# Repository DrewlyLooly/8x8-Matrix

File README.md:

# Adafruit-NeoPixel-8x8-Matrix 

__Format is KiCAD schematic and board layout__

Based directly on the Adafuit NeoPixel 8x8 Matrix, this design converts to KiCAD and facilitates direct use with the HAZE flagger kit

## License

Adafruit invests time and resources providing this open source design, 
please support Adafruit and open-source hardware by purchasing 
products from Adafruit!

Designed by Adafruit Industries, modified by Haze Engineering, LLC.  
Creative Commons Attribution, Share-Alike license, check license.txt for more information
All text above must be included in any redistribution

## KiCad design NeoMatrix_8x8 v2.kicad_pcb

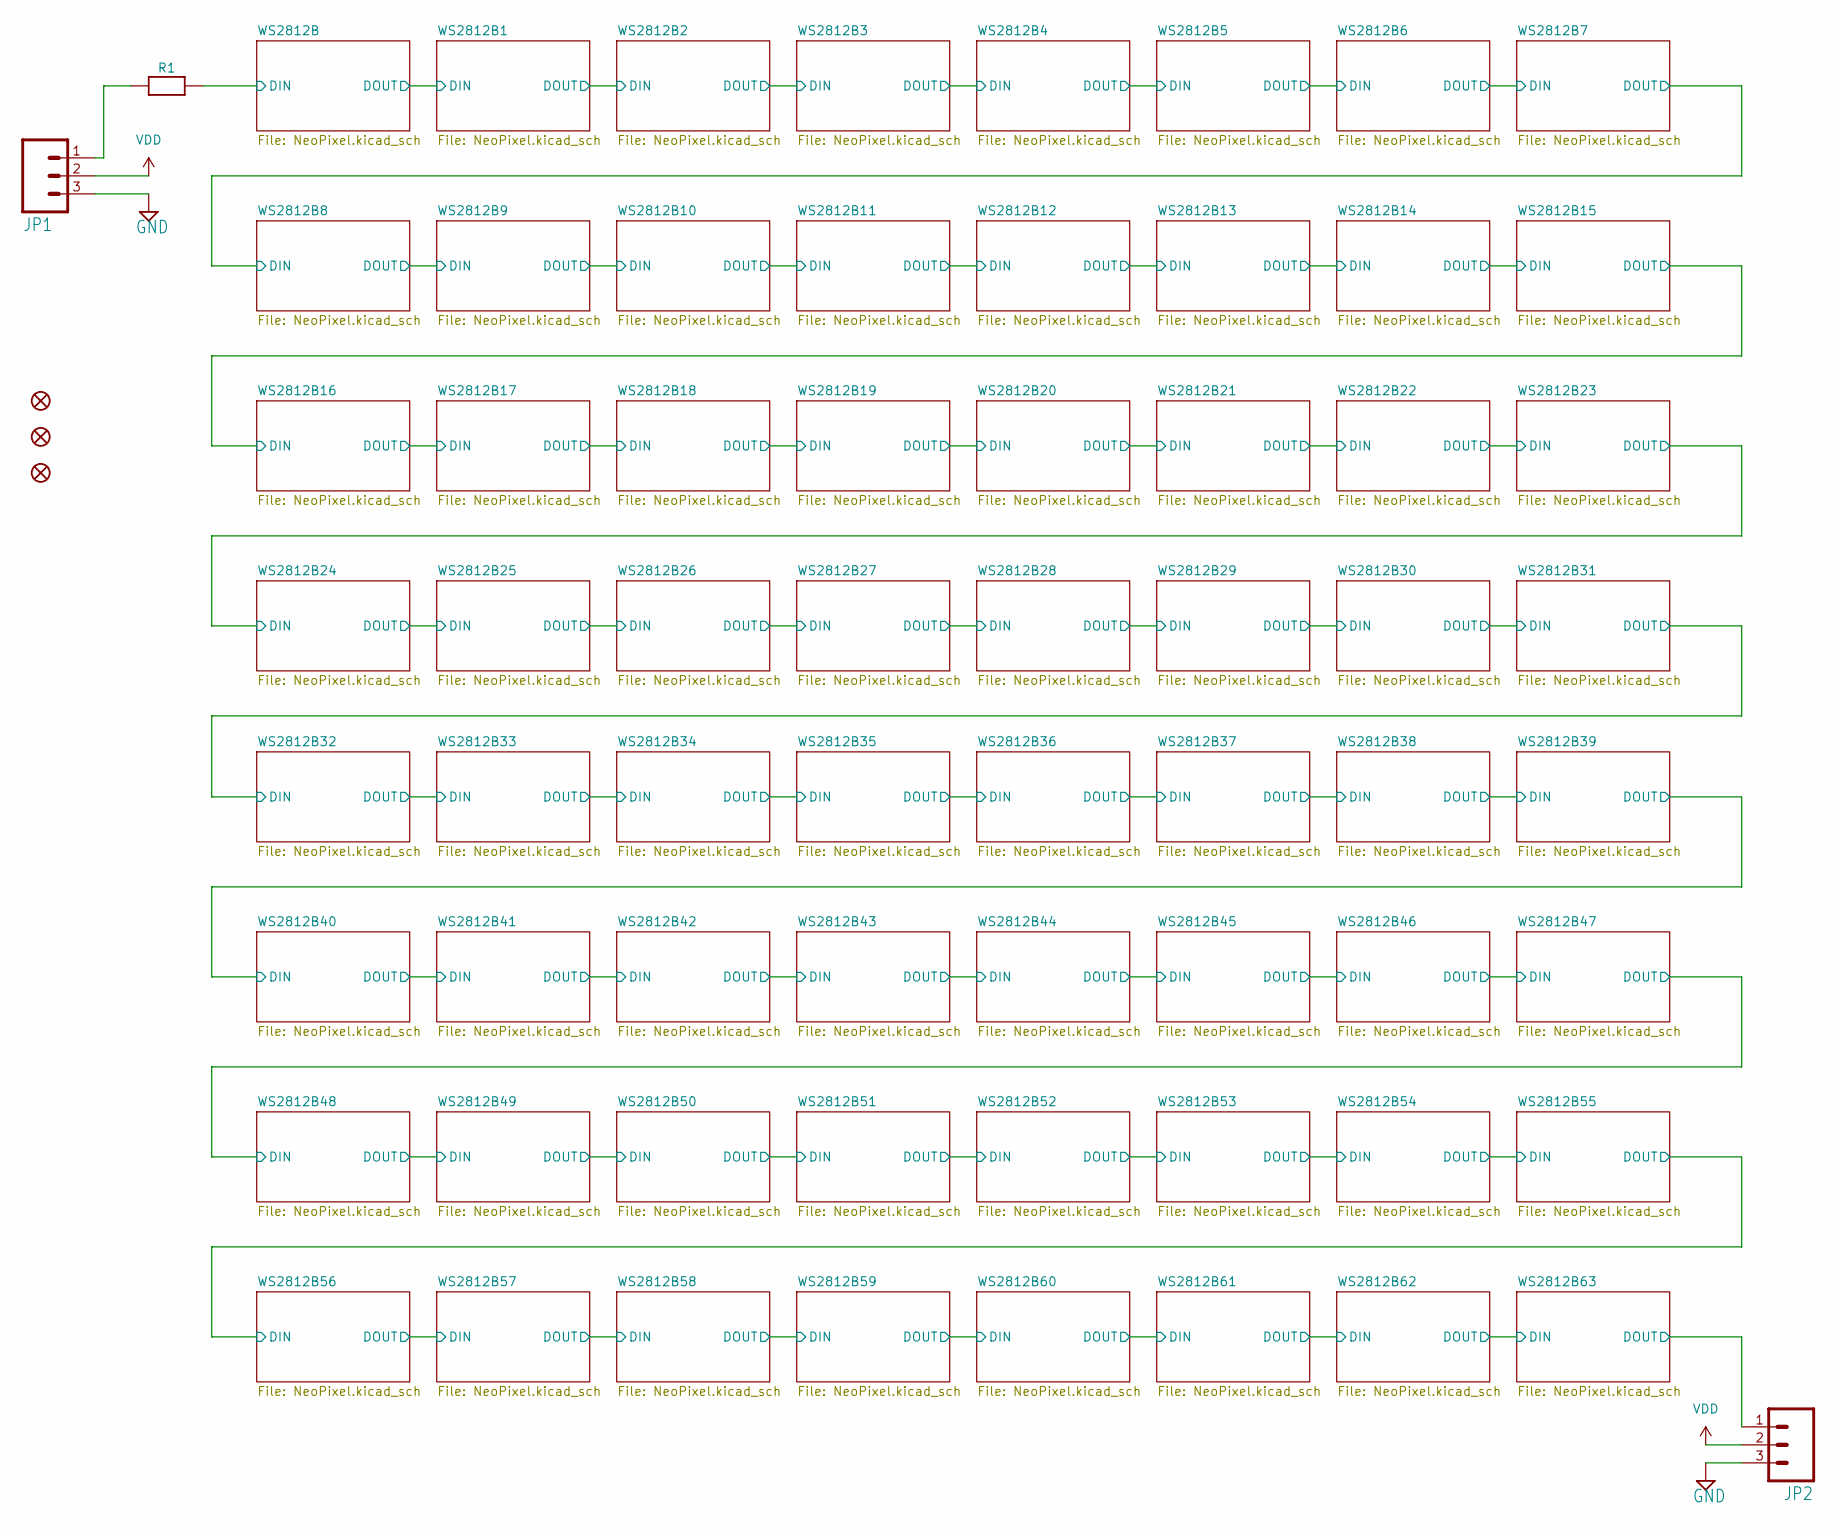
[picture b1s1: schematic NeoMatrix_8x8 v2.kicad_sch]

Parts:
FID1, FID2, FID3: FIDUCIAL""; FIDUCIAL_1MM
JP1, JP2: M03PTH; 1X03
R1: 470R; 0805-NO

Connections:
/WS2812B63/DOUT: JP2.1; also elsewhere on the board
/WS2812B/DIN: R1.2; also elsewhere on the board
GND: JP1.3, JP2.3; also elsewhere on the board
unnamed: JP1.1, R1.1
VDD: JP1.2, JP2.2; also elsewhere on the board

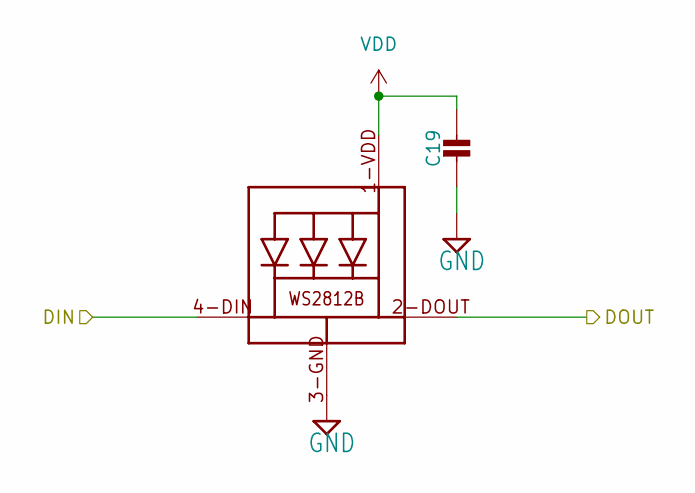
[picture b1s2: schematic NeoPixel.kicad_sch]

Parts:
C19: CAP_CERAMIC0805-NOOUTLINE; 0805-NO
LED19: WS2812B5050; WS2812B

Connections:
/WS2812B17/DOUT: LED19.4-DIN (DI); also elsewhere on the board
/WS2812B18/DOUT: LED19.2-DOUT (DO); also elsewhere on the board
GND: C19.2, LED19.3-GND (GND); also elsewhere on the board
VDD: C19.1, LED19.1-VDD (VDD); also elsewhere on the board

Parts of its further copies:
C1, C2, C3, C4, C5, C6, C7, C9, C10, C11, C12, C13, C14, C15, C17, C18, C20, C21, C22, C23, C25, C26, C27, C28, C29, C30, C31, C33, C34, C35, C36, C37, C38, C39, C41, C42, C43, C44, C45, C46, C47, C49, C50, C51, C52, C53, C54, C55, C57, C58, C59, C60, C61, C62, C63: CAP_CERAMIC0805-NOOUTLINE; 0805-NO
LED1, LED2, LED3, LED4, LED5, LED6, LED7, LED8, LED9, LED10, LED11, LED12, LED13, LED14, LED15, LED16, LED17, LED18, LED20, LED21, LED22, LED23, LED24, LED25, LED26, LED27, LED28, LED29, LED30, LED31, LED32, LED33, LED34, LED35, LED36, LED37, LED38, LED39, LED40, LED41, LED42, LED43, LED44, LED45, LED46, LED47, LED48, LED49, LED50, LED51, LED52, LED53, LED54, LED55, LED56, LED57, LED58, LED59, LED60, LED61, LED62, LED63, LED64: WS2812B5050; WS2812B

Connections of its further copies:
/WS2812B1/DOUT: LED2.2-DOUT (DO), LED3.4-DIN (DI)
/WS2812B2/DOUT: LED3.2-DOUT (DO), LED4.4-DIN (DI)
/WS2812B3/DOUT: LED4.2-DOUT (DO), LED5.4-DIN (DI)
/WS2812B4/DOUT: LED5.2-DOUT (DO), LED6.4-DIN (DI)
/WS2812B5/DOUT: LED6.2-DOUT (DO), LED7.4-DIN (DI)
/WS2812B6/DOUT: LED7.2-DOUT (DO), LED8.4-DIN (DI)
/WS2812B7/DOUT: LED8.2-DOUT (DO), LED9.4-DIN (DI)
/WS2812B8/DOUT: LED9.2-DOUT (DO), LED10.4-DIN (DI)
/WS2812B10/DIN: LED10.2-DOUT (DO), LED11.4-DIN (DI)
/WS2812B10/DOUT: LED11.2-DOUT (DO), LED12.4-DIN (DI)
/WS2812B11/DOUT: LED12.2-DOUT (DO), LED13.4-DIN (DI)
/WS2812B12/DOUT: LED13.2-DOUT (DO), LED14.4-DIN (DI)
/WS2812B13/DOUT: LED14.2-DOUT (DO), LED15.4-DIN (DI)
/WS2812B14/DOUT: LED15.2-DOUT (DO), LED16.4-DIN (DI)
/WS2812B15/DOUT: LED16.2-DOUT (DO), LED17.4-DIN (DI)
/WS2812B16/DOUT: LED17.2-DOUT (DO), LED18.4-DIN (DI)
/WS2812B17/DOUT: LED18.2-DOUT (DO); also elsewhere on the board
/WS2812B18/DOUT: LED20.4-DIN (DI); also elsewhere on the board
/WS2812B19/DOUT: LED20.2-DOUT (DO), LED21.4-DIN (DI)
/WS2812B20/DOUT: LED21.2-DOUT (DO), LED22.4-DIN (DI)
/WS2812B21/DOUT: LED22.2-DOUT (DO), LED23.4-DIN (DI)
/WS2812B22/DOUT: LED23.2-DOUT (DO), LED24.4-DIN (DI)
/WS2812B23/DOUT: LED24.2-DOUT (DO), LED25.4-DIN (DI)
/WS2812B24/DOUT: LED25.2-DOUT (DO), LED26.4-DIN (DI)
/WS2812B25/DOUT: LED26.2-DOUT (DO), LED27.4-DIN (DI)
/WS2812B26/DOUT: LED27.2-DOUT (DO), LED28.4-DIN (DI)
/WS2812B27/DOUT: LED28.2-DOUT (DO), LED29.4-DIN (DI)
/WS2812B28/DOUT: LED29.2-DOUT (DO), LED30.4-DIN (DI)
/WS2812B29/DOUT: LED30.2-DOUT (DO), LED31.4-DIN (DI)
/WS2812B30/DOUT: LED31.2-DOUT (DO), LED32.4-DIN (DI)
/WS2812B31/DOUT: LED32.2-DOUT (DO), LED33.4-DIN (DI)
/WS2812B32/DOUT: LED33.2-DOUT (DO), LED34.4-DIN (DI)
/WS2812B33/DOUT: LED34.2-DOUT (DO), LED35.4-DIN (DI)
/WS2812B34/DOUT: LED35.2-DOUT (DO), LED36.4-DIN (DI)
/WS2812B35/DOUT: LED36.2-DOUT (DO), LED37.4-DIN (DI)
/WS2812B36/DOUT: LED37.2-DOUT (DO), LED38.4-DIN (DI)
/WS2812B37/DOUT: LED38.2-DOUT (DO), LED39.4-DIN (DI)
/WS2812B38/DOUT: LED39.2-DOUT (DO), LED40.4-DIN (DI)
/WS2812B39/DOUT: LED40.2-DOUT (DO), LED41.4-DIN (DI)
/WS2812B40/DOUT: LED41.2-DOUT (DO), LED42.4-DIN (DI)
/WS2812B41/DOUT: LED42.2-DOUT (DO), LED43.4-DIN (DI)
/WS2812B42/DOUT: LED43.2-DOUT (DO), LED44.4-DIN (DI)
/WS2812B43/DOUT: LED44.2-DOUT (DO), LED45.4-DIN (DI)
/WS2812B44/DOUT: LED45.2-DOUT (DO), LED46.4-DIN (DI)
/WS2812B45/DOUT: LED46.2-DOUT (DO), LED47.4-DIN (DI)
/WS2812B46/DOUT: LED47.2-DOUT (DO), LED48.4-DIN (DI)
/WS2812B47/DOUT: LED48.2-DOUT (DO), LED49.4-DIN (DI)
/WS2812B48/DOUT: LED49.2-DOUT (DO), LED50.4-DIN (DI)
/WS2812B49/DOUT: LED50.2-DOUT (DO), LED51.4-DIN (DI)
/WS2812B50/DOUT: LED51.2-DOUT (DO), LED52.4-DIN (DI)
/WS2812B51/DOUT: LED52.2-DOUT (DO), LED53.4-DIN (DI)
/WS2812B52/DOUT: LED53.2-DOUT (DO), LED54.4-DIN (DI)
/WS2812B53/DOUT: LED54.2-DOUT (DO), LED55.4-DIN (DI)
/WS2812B54/DOUT: LED55.2-DOUT (DO), LED56.4-DIN (DI)
/WS2812B55/DOUT: LED56.2-DOUT (DO), LED57.4-DIN (DI)
/WS2812B56/DOUT: LED57.2-DOUT (DO), LED58.4-DIN (DI)
/WS2812B57/DOUT: LED58.2-DOUT (DO), LED59.4-DIN (DI)
/WS2812B58/DOUT: LED59.2-DOUT (DO), LED60.4-DIN (DI)
/WS2812B59/DOUT: LED60.2-DOUT (DO), LED61.4-DIN (DI)
/WS2812B60/DOUT: LED61.2-DOUT (DO), LED62.4-DIN (DI)
/WS2812B61/DOUT: LED62.2-DOUT (DO), LED63.4-DIN (DI)
/WS2812B62/DOUT: LED63.2-DOUT (DO), LED64.4-DIN (DI)
/WS2812B63/DOUT: LED64.2-DOUT (DO); also elsewhere on the board
/WS2812B/DIN: LED1.4-DIN (DI); also elsewhere on the board
/WS2812B/DOUT: LED1.2-DOUT (DO), LED2.4-DIN (DI)
GND: C1.2, C2.2, C3.2, C4.2, C5.2, C6.2, C7.2, C9.2, C10.2, C11.2, C12.2, C13.2, C14.2, C15.2, C17.2, C18.2, C20.2, C21.2, C22.2, C23.2, C25.2, C26.2, C27.2, C28.2, C29.2, C30.2, C31.2, C33.2, C34.2, C35.2, C36.2, C37.2, C38.2, C39.2, C41.2, C42.2, C43.2, C44.2, C45.2, C46.2, C47.2, C49.2, C50.2, C51.2, C52.2, C53.2, C54.2, C55.2, C57.2, C58.2, C59.2, C60.2, C61.2, C62.2, C63.2, LED1.3-GND (GND), LED2.3-GND (GND), LED3.3-GND (GND), LED4.3-GND (GND), LED5.3-GND (GND), LED6.3-GND (GND), LED7.3-GND (GND), LED8.3-GND (GND), LED9.3-GND (GND), LED10.3-GND (GND), LED11.3-GND (GND), LED12.3-GND (GND), LED13.3-GND (GND), LED14.3-GND (GND), LED15.3-GND (GND), LED16.3-GND (GND), LED17.3-GND (GND), LED18.3-GND (GND), LED20.3-GND (GND), LED21.3-GND (GND), LED22.3-GND (GND), LED23.3-GND (GND), LED24.3-GND (GND), LED25.3-GND (GND), LED26.3-GND (GND), LED27.3-GND (GND), LED28.3-GND (GND), LED29.3-GND (GND), LED30.3-GND (GND), LED31.3-GND (GND), LED32.3-GND (GND), LED33.3-GND (GND), LED34.3-GND (GND), LED35.3-GND (GND), LED36.3-GND (GND), LED37.3-GND (GND), LED38.3-GND (GND), LED39.3-GND (GND), LED40.3-GND (GND), LED41.3-GND (GND), LED42.3-GND (GND), LED43.3-GND (GND), LED44.3-GND (GND), LED45.3-GND (GND), LED46.3-GND (GND), LED47.3-GND (GND), LED48.3-GND (GND), LED49.3-GND (GND), LED50.3-GND (GND), LED51.3-GND (GND), LED52.3-GND (GND), LED53.3-GND (GND), LED54.3-GND (GND), LED55.3-GND (GND), LED56.3-GND (GND), LED57.3-GND (GND), LED58.3-GND (GND), LED59.3-GND (GND), LED60.3-GND (GND), LED61.3-GND (GND), LED62.3-GND (GND), LED63.3-GND (GND), LED64.3-GND (GND); also elsewhere on the board
VDD: C1.1, C2.1, C3.1, C4.1, C5.1, C6.1, C7.1, C9.1, C10.1, C11.1, C12.1, C13.1, C14.1, C15.1, C17.1, C18.1, C20.1, C21.1, C22.1, C23.1, C25.1, C26.1, C27.1, C28.1, C29.1, C30.1, C31.1, C33.1, C34.1, C35.1, C36.1, C37.1, C38.1, C39.1, C41.1, C42.1, C43.1, C44.1, C45.1, C46.1, C47.1, C49.1, C50.1, C51.1, C52.1, C53.1, C54.1, C55.1, C57.1, C58.1, C59.1, C60.1, C61.1, C62.1, C63.1, LED1.1-VDD (VDD), LED2.1-VDD (VDD), LED3.1-VDD (VDD), LED4.1-VDD (VDD), LED5.1-VDD (VDD), LED6.1-VDD (VDD), LED7.1-VDD (VDD), LED8.1-VDD (VDD), LED9.1-VDD (VDD), LED10.1-VDD (VDD), LED11.1-VDD (VDD), LED12.1-VDD (VDD), LED13.1-VDD (VDD), LED14.1-VDD (VDD), LED15.1-VDD (VDD), LED16.1-VDD (VDD), LED17.1-VDD (VDD), LED18.1-VDD (VDD), LED20.1-VDD (VDD), LED21.1-VDD (VDD), LED22.1-VDD (VDD), LED23.1-VDD (VDD), LED24.1-VDD (VDD), LED25.1-VDD (VDD), LED26.1-VDD (VDD), LED27.1-VDD (VDD), LED28.1-VDD (VDD), LED29.1-VDD (VDD), LED30.1-VDD (VDD), LED31.1-VDD (VDD), LED32.1-VDD (VDD), LED33.1-VDD (VDD), LED34.1-VDD (VDD), LED35.1-VDD (VDD), LED36.1-VDD (VDD), LED37.1-VDD (VDD), LED38.1-VDD (VDD), LED39.1-VDD (VDD), LED40.1-VDD (VDD), LED41.1-VDD (VDD), LED42.1-VDD (VDD), LED43.1-VDD (VDD), LED44.1-VDD (VDD), LED45.1-VDD (VDD), LED46.1-VDD (VDD), LED47.1-VDD (VDD), LED48.1-VDD (VDD), LED49.1-VDD (VDD), LED50.1-VDD (VDD), LED51.1-VDD (VDD), LED52.1-VDD (VDD), LED53.1-VDD (VDD), LED54.1-VDD (VDD), LED55.1-VDD (VDD), LED56.1-VDD (VDD), LED57.1-VDD (VDD), LED58.1-VDD (VDD), LED59.1-VDD (VDD), LED60.1-VDD (VDD), LED61.1-VDD (VDD), LED62.1-VDD (VDD), LED63.1-VDD (VDD), LED64.1-VDD (VDD); also elsewhere on the board

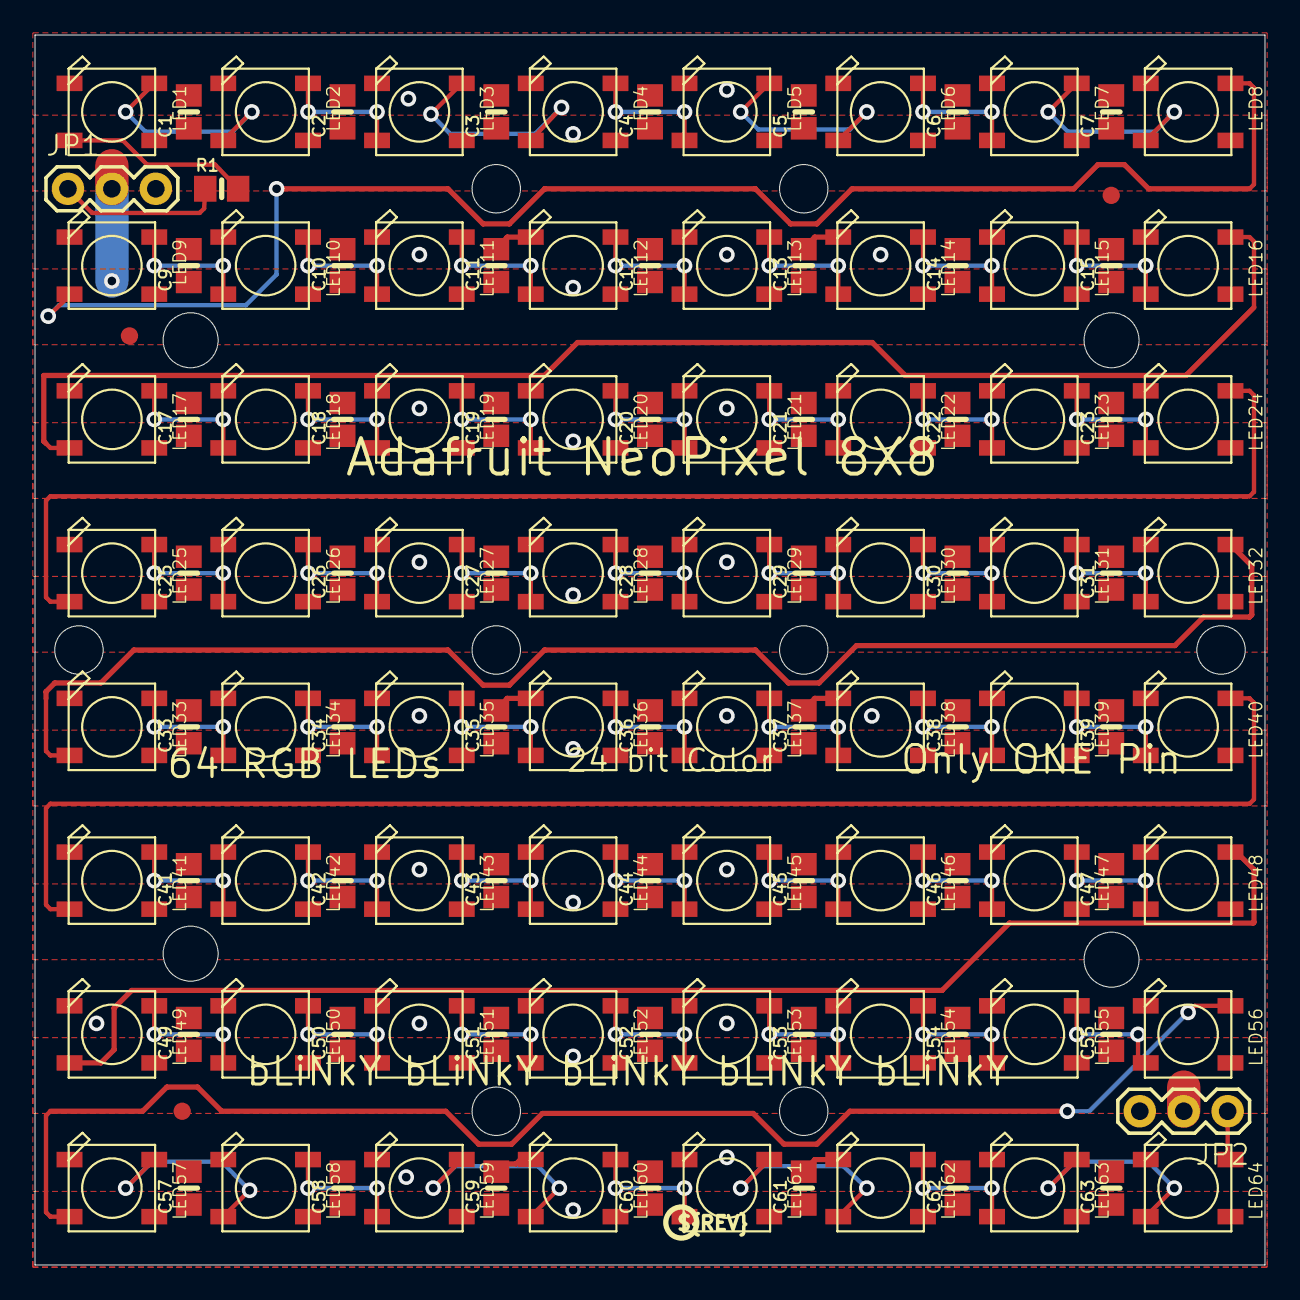
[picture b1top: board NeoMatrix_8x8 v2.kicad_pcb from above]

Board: 2 copper layers, 71.1 x 71.1 mm, 140 parts (1 on the bottom side), 68 nets.

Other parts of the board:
@HOLE0, @HOLE1, @HOLE2, @HOLE3, @HOLE4, @HOLE5, @HOLE6, @HOLE7, @HOLE8, @HOLE9, @HOLE10, @HOLE11: (no value)
U$1: ADAFRUIT_TEXT_30MM
U$2: PCBFEAT-REV-040

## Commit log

2025-04-02 Converted NeoMatrix to KiCAD
2025-04-02 Modified schematic to use blocks
2025-04-02 Libraries corrected, references updated
2025-04-05 Revised mounting holes and layout
